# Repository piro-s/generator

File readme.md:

### generator  [OnHold]

#### Description device:  
The pulse generator, implemented on STM32, can generate:  
1. continuous pulse generation;  
2. generation of pulse bursts.  

Init mode:
- width - 1 us;  
- period - 10 us;  
- pack period - 100 us;  
- number of impulses - 5.  

Max number of impulses in package - 2048.  
Min pulse width 100 ns.  
Control from a computer via RS-232 (J8) interface or via UART-USB adapter (J6).  
The development of the device is suspended, the plans are:  
- firmware for analog channel;  
- saving data to a separate EEPROM (scheme and firmware);  
- firmware for LCD and keyboard;
- new version of the case.  

#### PC program description:
The program allows you to customize the set values for the generator.  
For use:  
- linux: run generator_pyGui.py  
- windows: run dist/generator_pyGui.exe  

Setup:  
1. Select the COM port to which the device is connected from the drop-down list:  
  
2. By default, the generator runs in init mode. The current parameters are  
written in the current field. By pressing the button "Get parameters" you can  
get the current set values.  
  
If there is no data exchange with the generator, then there will be dashes in  
this field, there will also be errors in the log field.  
  
3. The generator parameters are set in order, that is, the pulse duration and  
its period, the burst period (set in any case, even if not needed), the number  
of pulses are set separately, if the number of pulses is 0, then there will be  
a constant generation of pulses, without a burst.  
The name of the parameter is signed in the figure:  
  
If something is entered incorrectly, or some other error occurs, everything  
will be displayed in the log field.  
  
4. If the wrong COM port was selected, then you can switch to the "Setup" tab,  
  
select "Disconnect", click "Refresh", select the required COM port from the  
drop-down list, and click the "Connect" button, you can go back to the  
"Impulse" tab.  

The protocol for data exchange between the device and the PC is  
[here](https://htmlpreview.github.io/?https://github.com/piro-s/generator/blob/master/docs/protocol.html).  

#### Scheme  
[scheme_v3.2_pdf](docs/scheme/scheme_v3.2.pdf)  

#### Case  
Prototype case for v3.2 generator board (case will fit next versions).  
  
Errors:  
- the two diagonal posts interfere with the connectors.

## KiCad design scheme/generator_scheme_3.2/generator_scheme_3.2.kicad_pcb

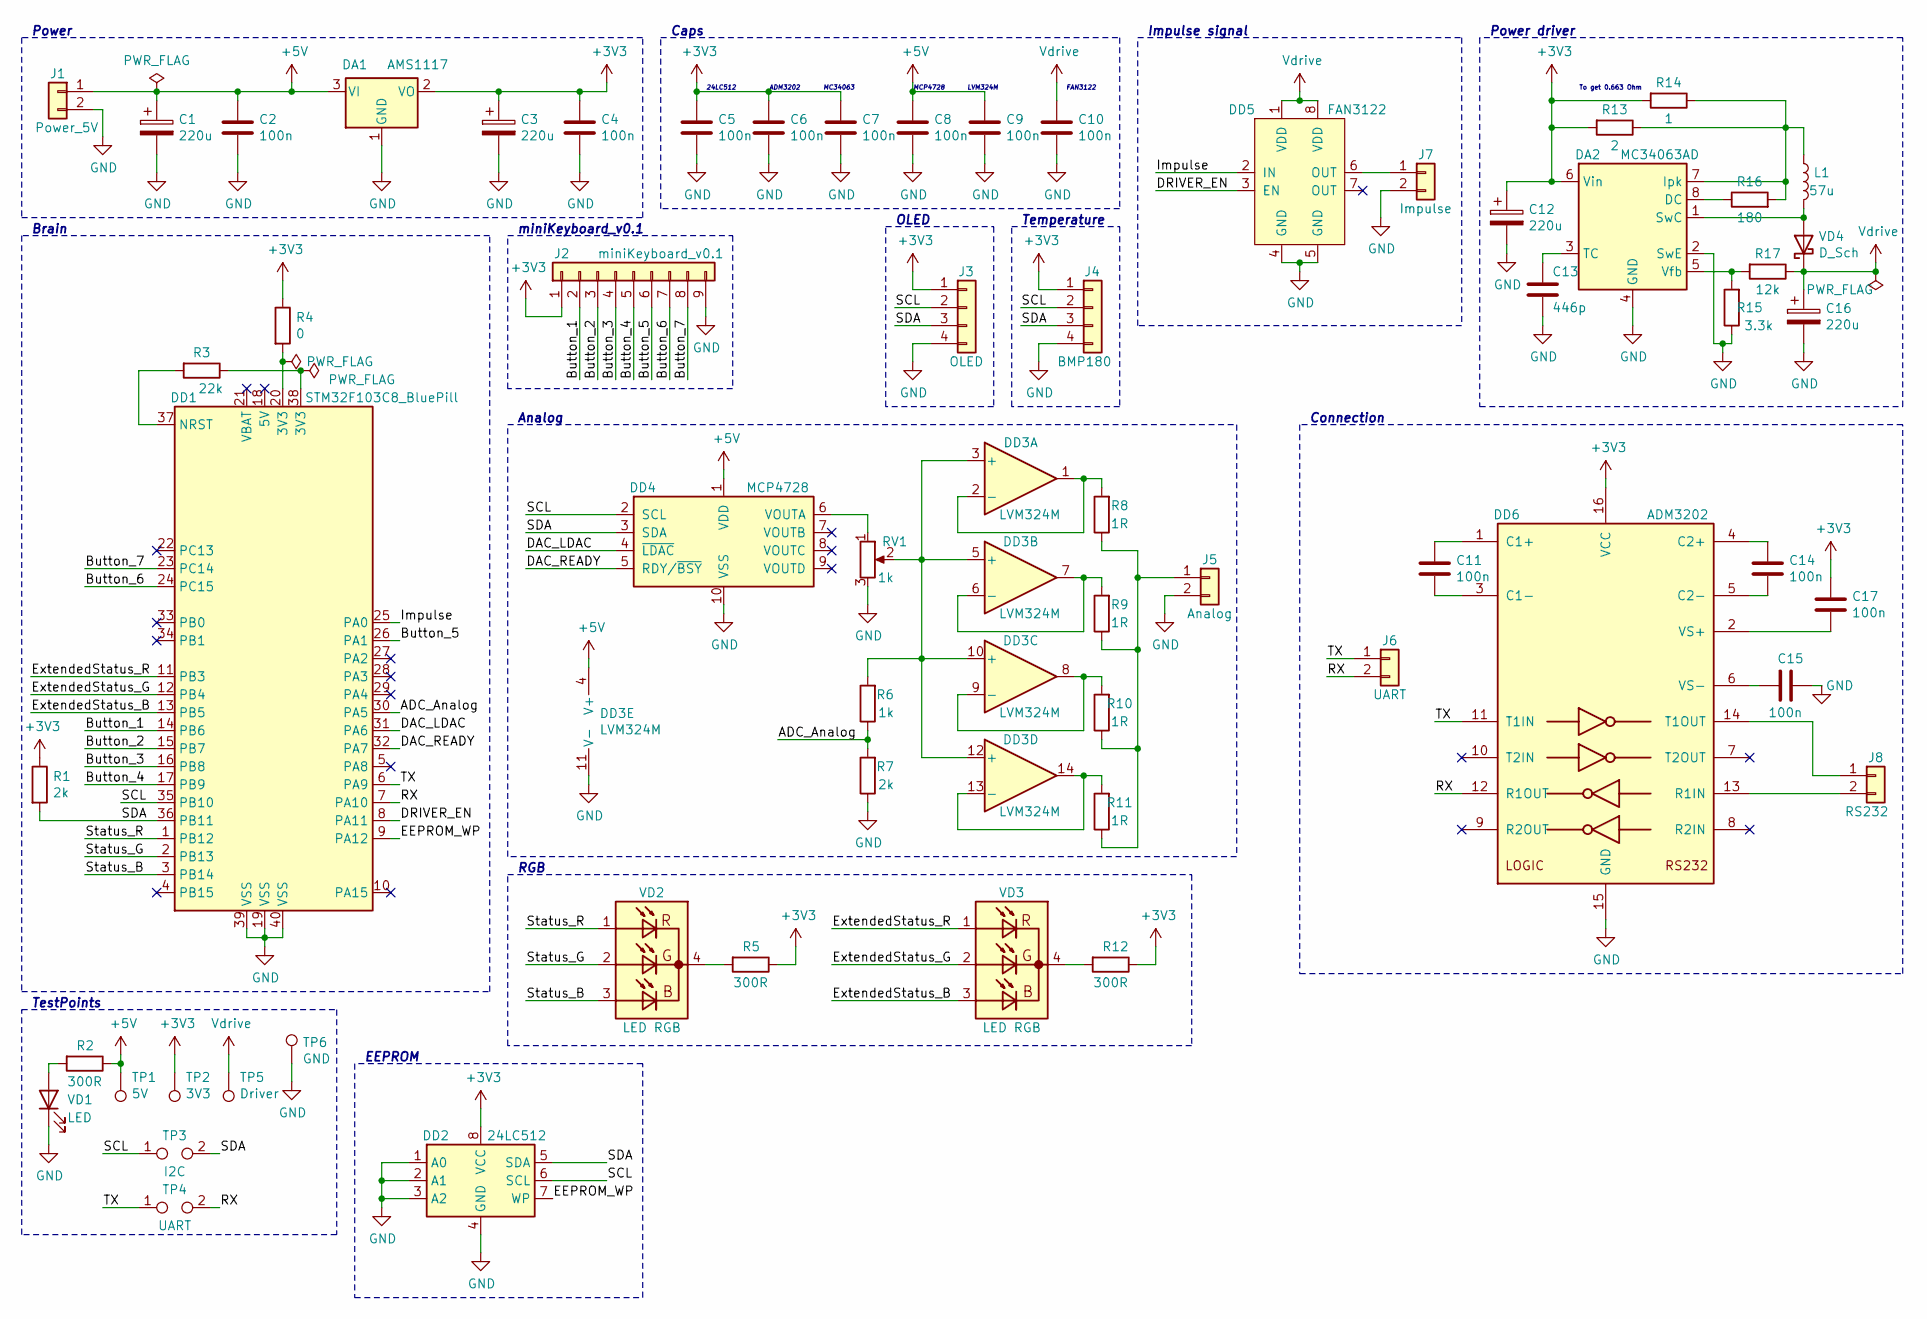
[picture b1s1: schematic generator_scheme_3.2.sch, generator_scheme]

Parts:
C1, C3, C12, C16: 220u; CP_EIA-7260-15_AVX-R_Pad2.68x6.30mm_HandSolder
C2, C4, C5, C6, C7, C8, C9, C10, C11, C14, C15, C17: 100n; C_0402_1005Metric
C13: 446p; C_0402_1005Metric
DA1: AMS1117; SOT-223-3_TabPin2
DA2: MC34063AD; SOIC-8_3.9x4.9mm_P1.27mm
DD1: STM32F103C8_BluePill
DD2: 24LC512; SOIC-8_3.9x4.9mm_P1.27mm
DD3: LVM324M; SOIC-14_3.9x8.7mm_P1.27mm
DD4: MCP4728; MSOP-10_3x3mm_P0.5mm
DD5: FAN3122; SOIC-8_3.9x4.9mm_P1.27mm
DD6: ADM3202; SO-16_3.9x9.9mm_P1.27mm
J1: Power_5V; PinHeader_1x02_P2.54mm_Vertical
J2: miniKeyboard_v0.1; PinSocket_1x09_P2.54mm_Vertical
J3: OLED; PinHeader_1x04_P2.54mm_Vertical
J4: BMP180; PinHeader_1x04_P2.54mm_Vertical
J5: Analog; PinHeader_1x02_P2.54mm_Vertical
J6: UART; PinHeader_1x02_P2.54mm_Vertical
J7: Impulse; PinHeader_1x02_P2.54mm_Vertical
J8: RS232; PinHeader_1x02_P2.54mm_Vertical
L1: 57u; L_7.3x7.3_H4.5
R1, R7: 2k; R_0402_1005Metric
R2, R5, R12: 300R; R_0402_1005Metric
R3: 22k; R_0402_1005Metric
R4: 0; R_0402_1005Metric
R6: 1k; R_0402_1005Metric
R8, R9, R10, R11: 1R; R_0402_1005Metric
R13: 2; R_0402_1005Metric
R14: 1; R_0402_1005Metric
R15: 3.3k; R_0402_1005Metric
R16: 180; R_0402_1005Metric
R17: 12k; R_0402_1005Metric
RV1: 1k; PinHeader_1x03_P1.27mm_Vertical
TP1: 5V; TestPoint_Keystone_5000-5004_Miniature
TP2: 3V3; TestPoint_Keystone_5000-5004_Miniature
TP3: I2C; TestPoint_2Pads_Pitch2.54mm_Drill0.8mm
TP4: UART; TestPoint_2Pads_Pitch2.54mm_Drill0.8mm
TP5: Driver; TestPoint_Keystone_5000-5004_Miniature
TP6: GND; TestPoint_Keystone_5000-5004_Miniature
VD1: LED; PinHeader_1x02_P2.54mm_Vertical
VD2, VD3: LED RGB; PinHeader_1x04_P1.27mm_Vertical
VD4: D_Sch; D_0603_1608Metric

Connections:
+3V3: C3.1, C4.1, C5.1, C6.1, C7.1, C12.1, C17.1, DA1.2 (VO), DA2.6 (Vin), DD2.8 (VCC), DD6.16 (VCC), J2.1, J3.1, J4.1, R1.1, R4.1, R5.1, R12.1, R13.2, R14.2, TP2.1
+5V: C1.1, C2.1, C8.1, C9.1, DA1.3 (VI), DD3.4 (V+), DD4.1 (VDD), J1.1, R2.1, TP1.1
/ADC_Analog: DD1.30 (PA5), R6.1, R7.2
/Button_1: DD1.14 (PB6), J2.2
/Button_2: DD1.15 (PB7), J2.3
/Button_3: DD1.16 (PB8), J2.4
/Button_4: DD1.17 (PB9), J2.5
/Button_5: DD1.26 (PA1), J2.6
/Button_6: DD1.24 (PC15), J2.7
/Button_7: DD1.23 (PC14), J2.8
/DAC_LDAC: DD1.31 (PA6), DD4.4 (~LDAC)
/DAC_READY: DD1.32 (PA7), DD4.5 (RDY/~BSY)
/DRIVER_EN: DD1.8 (PA11), DD5.3 (EN)
/EEPROM_WP: DD1.9 (PA12), DD2.7 (WP)
/ExtendedStatus_B: DD1.13 (PB5), VD3.3 (AB)
/ExtendedStatus_G: DD1.12 (PB4), VD3.2 (AG)
/ExtendedStatus_R: DD1.11 (PB3), VD3.1 (AR)
/Impulse: DD1.25 (PA0), DD5.2 (IN)
/RX: DD1.7 (PA10), DD6.12 (R1OUT), J6.2, TP4.2
/SCL: DD1.35 (PB10), DD2.6 (SCL), DD4.2 (SCL), J3.2, J4.2, TP3.1
/SDA: DD1.36 (PB11), DD2.5 (SDA), DD4.3 (SDA), J3.3, J4.3, R1.2, TP3.2
/Status_B: DD1.3 (PB14), VD2.3 (AB)
/Status_G: DD1.2 (PB13), VD2.2 (AG)
/Status_R: DD1.1 (PB12), VD2.1 (AR)
/TX: DD1.6 (PA9), DD6.11 (T1IN), J6.1, TP4.1
GND: C1.2, C2.2, C3.2, C4.2, C5.2, C6.2, C7.2, C8.2, C9.2, C10.2, C12.2, C13.2, C15.1, C16.2, DA1.1 (GND), DA2.2 (SwE), DA2.4 (GND), DD1.19 (VSS), DD1.39 (VSS), DD1.40 (VSS), DD2.1 (A0), DD2.2 (A1), DD2.3 (A2), DD2.4 (GND), DD3.11 (V-), DD4.10 (VSS), DD5.4 (GND), DD5.5 (GND), DD6.15 (GND), J1.2, J2.9, J3.4, J4.4, J5.2, J7.2, R7.1, R15.1, RV1.3, TP6.1, VD1.1 (K)
unnamed: C11.1, DD6.1 (C1+)
unnamed: C11.2, DD6.3 (C1-)
unnamed: C13.1, DA2.3 (TC)
unnamed: C14.1, DD6.4 (C2+)
unnamed: C14.2, DD6.5 (C2-)
unnamed: C15.2, DD6.6 (VS-)
unnamed: C17.2, DD6.2 (VS+)
unnamed: DA2.1 (SwC), L1.2, VD4.2 (A)
unnamed: DA2.5 (Vfb), R15.2, R17.2
unnamed: DA2.7 (Ipk), L1.1, R13.1, R14.1, R16.2
unnamed: DA2.8 (DC), R16.1
unnamed: DD1.20 (3V3), R4.2
unnamed: DD1.37 (NRST), R3.2
unnamed: DD1.38 (3V3), R3.1
unnamed: DD3.1, DD3.2 (-), R8.2
unnamed: DD3.6 (-), DD3.7, R9.2
unnamed: DD3.8, DD3.9 (-), R10.2
unnamed: DD3.3 (+), DD3.5 (+), DD3.10 (+), DD3.12 (+), R6.2, RV1.2
unnamed: DD3.13 (-), DD3.14, R11.2
unnamed: DD4.6 (VOUTA), RV1.1
unnamed: DD5.6 (OUT), J7.1
unnamed: DD6.13 (R1IN), J8.2
unnamed: DD6.14 (T1OUT), J8.1
unnamed: J5.1, R8.1, R9.1, R10.1, R11.1
unnamed: R2.2, VD1.2 (A)
unnamed: R5.2, VD2.4 (C)
unnamed: R12.2, VD3.4 (C)
Vdrive: C10.1, C16.1, DD5.1 (VDD), DD5.8 (VDD), R17.1, TP5.1, VD4.1 (K)

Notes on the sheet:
EEPROM
Power
To get 0.663 Ohm
Power driver
Brain
Connection
Impulse signal
ADM3202
24LC512
Temperature
RGB
MC34063
MCP4728
FAN3122
LVM324M
Analog
Caps
TestPoints
OLED
miniKeyboard_v0.1

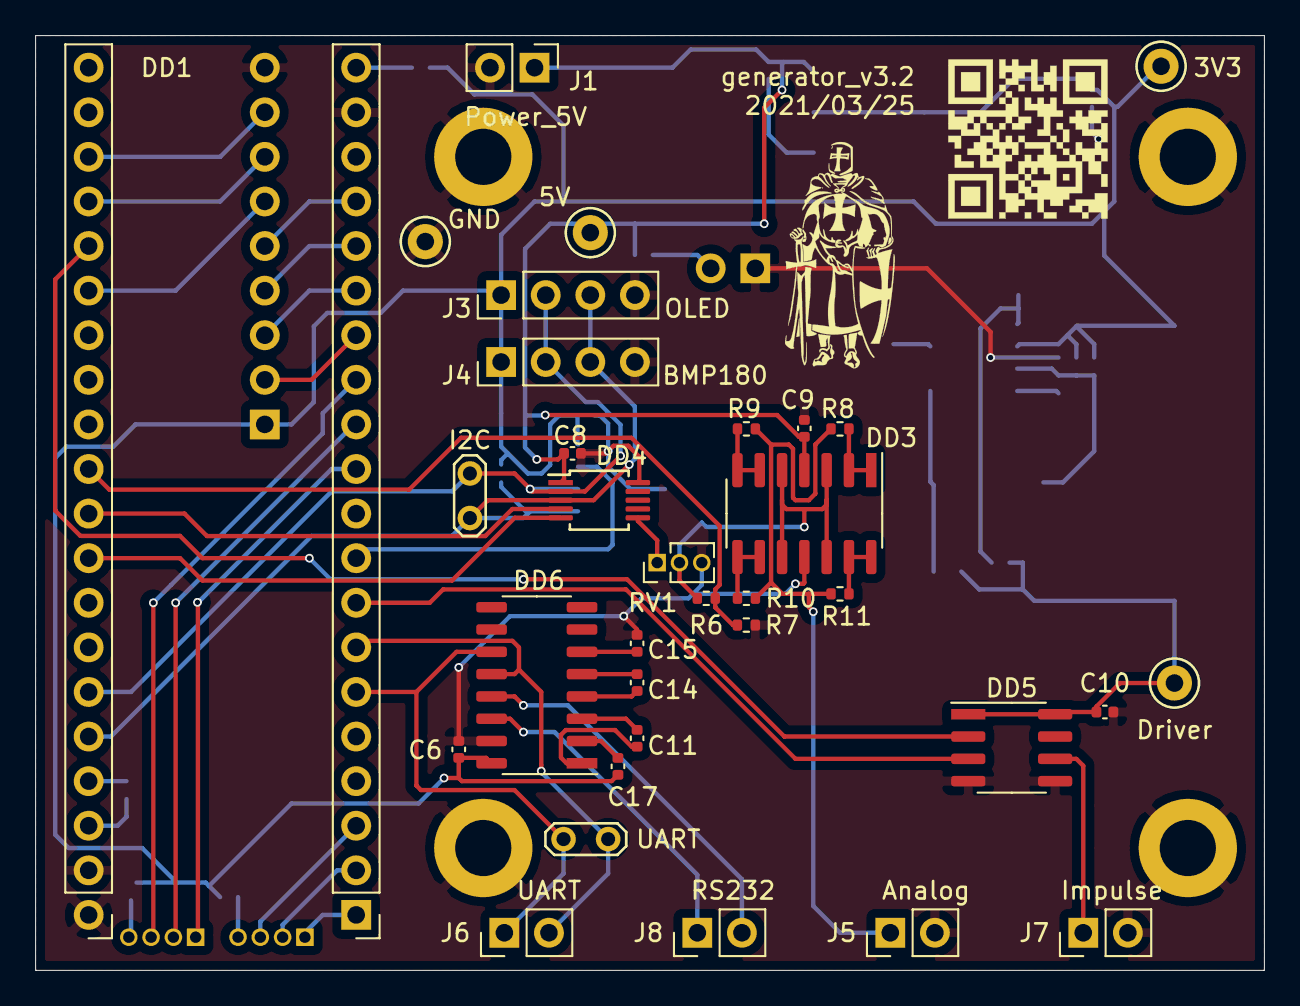
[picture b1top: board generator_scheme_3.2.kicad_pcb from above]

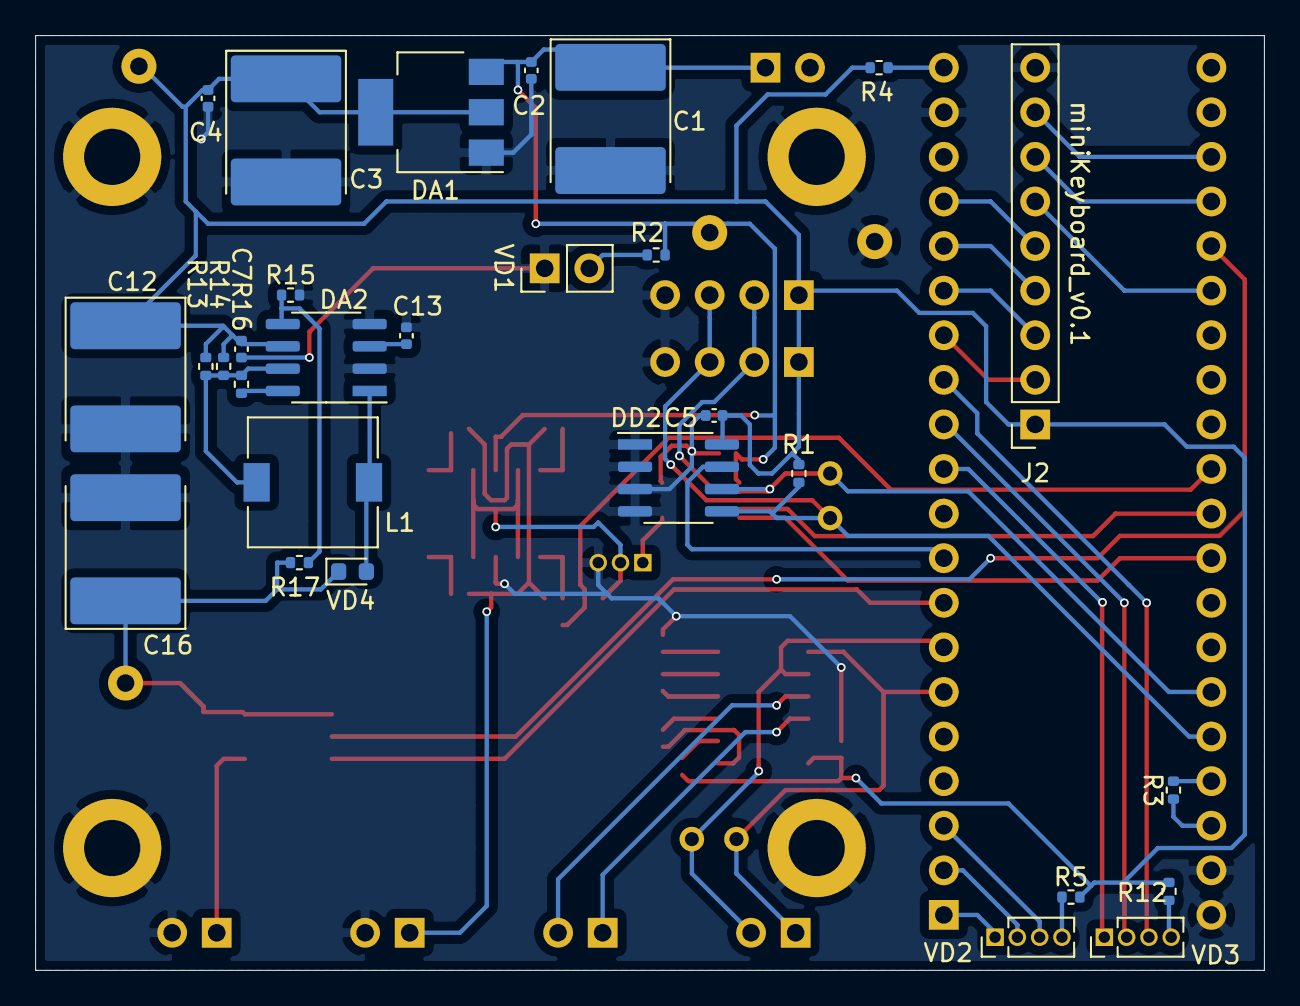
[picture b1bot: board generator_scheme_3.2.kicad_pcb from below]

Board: 2 copper layers, 70.0 x 53.2 mm, 62 parts (29 on the bottom side), 54 nets.

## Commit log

2022-01-18 Device program
    generator_v2
2022-01-18 PC program
    for linux user: run generator_pyGui.py
    for windows user: run dist/generator_pyGui.exe
2022-01-18 Scheme
    scheme for v3.2
2022-01-18 docs: PC program
    added protocol between device and PC
2022-01-18 Case
    added case prototype
2022-01-18 docs: datasheets
2022-01-18 docs: readme.md
2022-01-18 docs: scheme
